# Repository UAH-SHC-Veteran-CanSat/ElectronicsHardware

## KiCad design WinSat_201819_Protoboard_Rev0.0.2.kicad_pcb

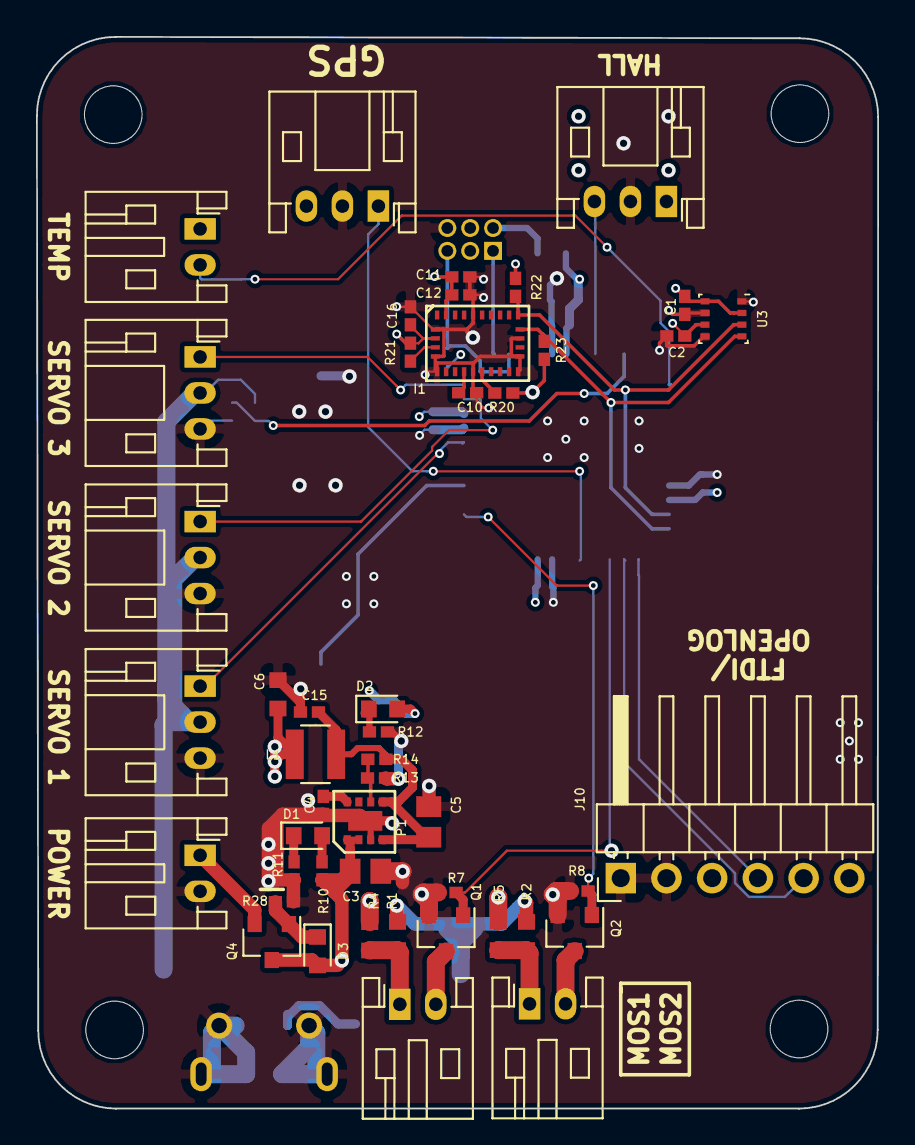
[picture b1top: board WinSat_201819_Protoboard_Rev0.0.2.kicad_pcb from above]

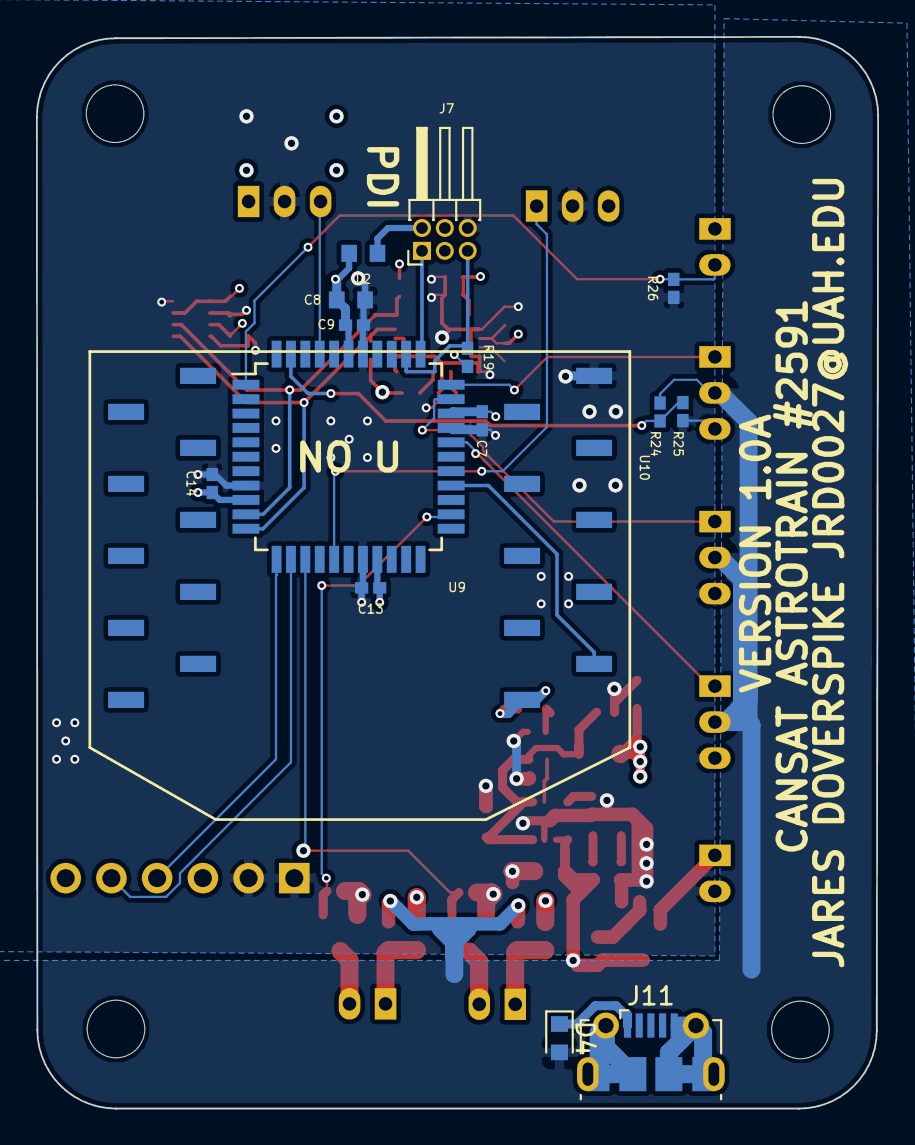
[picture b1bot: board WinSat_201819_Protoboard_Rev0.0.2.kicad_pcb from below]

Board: 4 copper layers, 46.7 x 59.5 mm, 66 parts (15 on the bottom side), 36 nets.

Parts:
C1, C2, C7, C9, C10, C13, C14, C15, C16: 100nF; Not_Broken_0402
C3: 10uF; C_0805_2012Metric
C4: 390pF; Not_Broken_0402
C5: 22uF; C_0805_2012Metric
C6, C8: 10uF; C_0603_1608Metric
C11: 6.8nF; Not_Broken_0402
C12: 12OnF; Not_Broken_0402
D1: LED Red; LED_0603_1608Metric
D2: LED Blue; LED_0603_1608Metric
D3, D4: DIODE; D_0603_1608Metric
I1: BNO055
J1, J2, J4, J6: Conn_01x02_Female; JST_PH_S2B-PH-K_1x02_P2.00mm_Horizontal
J3, J5, J8, J9, J12: Conn_01x03_Female; JST_PH_S3B-PH-K_1x03_P2.00mm_Horizontal
J7: JTAG-6PIN; PinHeader_2x03_P1.27mm_Horizontal
J10: Conn_01x06_Male; PinHeader_1x06_P2.54mm_Horizontal
J11: USB_B_Micro; USB_Micro-B_Molex-105017-0001
L1: 22uH; L_Abracon_ASPI-3012S
L2: 220OHM 100MHZ; L_0603_1608Metric
MK1, MK2, MK3, MK4: Mounting_Hole; MountingHole_3.2mm_M3
P1: TPS82150
Q1, Q2: SSM3K329R; SOT-23
Q4: Package_TO_SOT_SMD:SOT-23; SOT-23
R1, R2, R4, R5: 0 OHM; R_0603_1608Metric
R7, R8, R24, R28: 100K; Not_Broken_0402
R10, R11, R12: 400 OHM; Not_Broken_0402
R13: 100k; Not_Broken_0402
R14: 309k; Not_Broken_0402
R19, R20, R21: 10K; Not_Broken_0402
R22, R23: 4.7K; Not_Broken_0402
R25: 7.15K; Not_Broken_0402
R26: 66K; Not_Broken_0402
U3: BMP280; Bosch_LGA-8_2.5x2.5mm_Pitch0.65mm_ClockwisePinNumbering
U9: ATxmega128A4-AU; TQFP-44_10x10mm_P0.8mm
U10: XBEE_PRO900

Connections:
+3V3: C1.1, C2.1, C6.1, C7.1, C11.2, C12.2, C13.1, C14.1, C16.2, D2.2, I1.3, I1.28, J5.1, J6.1, J7.2, J9.3, J10.3, L1.2, L2.1, R4.2, R5.2, R19.2, R20.1, R21.1, R22.1, R23.1, U3.2, U3.6, U3.8, U9.9, U9.19, U9.31, U10.1
BAT_POS: C3.1, D3.2, D4.2, J3.2, J8.2, J12.2, P1.1, P1.2, Q4.3, R1.2, R2.2, R10.1, R24.2
FTDI_OLOG_RX-MCU_TX: J10.5, U9.13
FTDI_OLOG_TX-MCU_RX: J10.4, U9.12
GND: C1.2, C2.2, C3.2, C4.1, C5.2, C6.2, C7.2, C8.2, C9.1, C10.1, C11.1, C12.1, C13.2, C14.2, C15.2, C16.1, I1.2, I1.5, I1.6, I1.10, I1.15, I1.16, I1.18, I1.25, J3.3, J4.2, J5.2, J7.6, J8.3, J9.2, J10.1, J10.2, J11.5, J11.6, J12.3, P1.3, P1.9, Q1.2, Q2.2, R7.2, R8.2, R11.2, R12.2, R13.2, R25.1, R26.1, R28.2, U3.1, U3.5, U3.7, U9.8, U9.18, U9.30, U9.38, U10.10
GPS_TX-MCU_RX: J9.1, U9.16
IMU_nRESET: I1.11, R20.2
MOSFET0_GPIO: Q1.1, R7.1, U9.14
MOSFET1_GPIO: Q2.1, R8.1, U9.24
unnamed: C4.2, P1.8
unnamed: C8.1, C9.2, L2.2, U9.39
unnamed: C10.2, I1.9
unnamed: C5.1, C15.1, L1.1, P1.4, P1.5, R14.2
unnamed: D1.1, R11.1
unnamed: D1.2, R10.2
unnamed: D2.1, R12.1
unnamed: D3.1, Q4.1, R28.1
unnamed: D4.1, J11.1
unnamed: I1.4, R21.2
unnamed: J1.1, R1.1, R4.1
unnamed: J1.2, Q1.3
unnamed: J2.1, R2.1, R5.1
unnamed: J2.2, Q2.3
unnamed: J4.1, Q4.2
unnamed: J7.1, U9.34
unnamed: J7.5, R19.1, U9.35
unnamed: P1.6, R13.1, R14.1
SCL1: I1.19, R23.2, U3.4, U9.11
SDA1: I1.20, R22.2, U3.3, U9.10
SERVO_TCL_1: J8.1, U9.29
SERVO_TCL_2: J3.1, U9.32
SERVO_TCL_3: J12.1, U9.33
TACH_ADC: J5.3, U9.41
TEMP_SENSE-ADC: J6.2, R26.2, U9.1
VOLTDIV_ADC: R24.1, R25.2, U9.43
XBEE_TX-MCU_RX: U9.26, U10.2

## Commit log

2018-11-13 First Revision
    Has not been vetted to be correct.
    Big things to check:
    -Make sure I did not mirror footprint/symbol
    -Mosfets
    -Can I hook up the LEDs the way I did
    -Be 100% sure the GPS does not need supporting hardware
2018-11-13 Library fixes and symbol cleanup
2018-11-13 Fixed JTAG reference prefix
2018-11-13 Fix library location
2018-11-13 net to power and pcb updates
2018-11-13 Near Complete Prototype
    Still needed:
    Camera Control
    Servo Control
    Ground Plane
2018-11-13 V1.0.0
    First Complete Revision
    To Do:
    -Double check schematic and PCB
    -Increase width of some data lines
    -Add ESD Protection
    --Resistor and Diodes
2018-11-13 V1.1.0 GPS Module Change
2018-11-13 V1.1.1 1M ESD
2018-11-13 Fixed XBee 3D model
2018-11-13 Added 3D model for SAM-M8Q
2018-11-13 Added GPS JST
2018-11-13 Little clean up around bno055
2018-11-13 GPS to 3 pin and board shrinkage
2018-11-13 FTDI Added
2018-11-13 Fix mounting hole position
2018-11-13 Say "Basically Nothing"
2018-11-13 Revert "Merge branch 'master' of https://github.com/UAH-SHC-Veteran-CanSat/ElectronicsHardware"
    This reverts commit f53a1c8a621f173f59d167d466539f6731bbe820, reversing
    changes made to 5a58aea797620e8d84e5d98f107fa16ded4ab213.
2018-11-13 Revert "Say "Basically Nothing""
    This reverts commit 5a58aea797620e8d84e5d98f107fa16ded4ab213.
2018-11-14 Redid what was broken.
2018-11-14 ESD PROTECTION
2018-11-14 Swapped BMP388 for BMP280
    Also why are your vias so big Jares?
2018-11-14 Ran a track cleanup
2018-11-14 Made the reference designators smaller so we can actually fit them places
2018-11-14 Cleaned up a few traces, fixed shoddy decoupling
    Also moved BMP180 away from openlog header
2018-11-20 Proto Final?
2018-11-20 Tiny schematic symbol cleanup
2018-11-20 Fixed Issues Thomas Saw
2018-11-20 Not sure what updated.
2018-11-28 Fixed a label
2019-01-24 Change Board Size
2019-02-13 Make sure updated
2019-02-14 Bye Overcurrent
